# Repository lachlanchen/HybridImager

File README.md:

[English](README.md) · [العربية](i18n/README.ar.md) · [Español](i18n/README.es.md) · [Français](i18n/README.fr.md) · [日本語](i18n/README.ja.md) · [한국어](i18n/README.ko.md) · [Tiếng Việt](i18n/README.vi.md) · [中文 (简体)](i18n/README.zh-Hans.md) · [中文（繁體）](i18n/README.zh-Hant.md) · [Deutsch](i18n/README.de.md) · [Русский](i18n/README.ru.md)

# HybridImager

*Open hybrid scientific imaging: single-pixel, event, frame, and spectral sensing in one maintainable research stack.*

HybridImager is a research and design workspace for a mixed scientific detector. The concept combines a high-dynamic-range single-pixel bucket detector, event-camera timing, frame-camera texture, and optional spectral measurements under one synchronized data model.

<!-- support:start -->

<!-- support:end -->

## System Concept

- **Single-pixel branch:** a central low-noise detector/TIA path for absolute intensity, high dynamic range, and spectral or coded measurements.
- **Event branch:** asynchronous temporal contrast from commercial event cameras first, then open FPGA interfaces when practical.
- **Frame branch:** global-shutter frame modules for texture, calibration, and human-readable inspection.
- **Fusion layer:** timestamped streams with exposure, gain, calibration profile, trigger, and pattern metadata.

## V1 Sensor Board

The first board draft is a KiCad-generated **Weiqi sparse sensor carrier** with 21 single-pixel detector sites, not one central bucket only. It includes per-site signal pads, explicit ground routing, three AFE placeholders, a QFN timing placeholder, SMA sync in/out, power/sync header, and a 2x20 expansion header for later event/frame/tile work.

Review package: [`hardware/v1-weiqi-sensor/`](hardware/v1-weiqi-sensor/) contains the KiCad board, dataset, BOM, clean DRC JSON, STEP model, Gerbers, drill files, and full-view renders.

## V2 ALS-PT19 Matrix

V2 is a dense `32x32` sensor-board draft using the `ALS-PT19` phototransistor family from the `CustomSensor`/digiOBSCURA reference. Unlike the older 45-degree, 2.0 mm layout, V2 uses unrotated footprints on a `2.54 mm` pitch so each sensor pad, row header pin, and column header pin is aligned and routable.

Review package: [`hardware/v2-als-pt19-32x32/`](hardware/v2-als-pt19-32x32/) contains the KiCad board, CustomSensor source dataset, BOM, clean DRC JSON, STEP model, Gerbers, drill files, and full-view renders.

## Current Contents

| Area | Location |
| --- | --- |
| Concept paper | `publications/hybrid_camera_concept.pdf` |
| Open camera survey | `publications/open_camera_project_survey.pdf` |
| V1 sparse sensor board | `hardware/v1-weiqi-sensor/` |
| V2 aligned ALS-PT19 matrix | `hardware/v2-als-pt19-32x32/` |
| Research notes | `references/` |
| Deterministic diagrams | `figures/hybrid_board_layout.*`, `figures/hybrid_signal_chain.*` |
| Hardware plan | `hardware/board_architecture.md` |
| Reconstruction plan | `algorithms/reconstruction_plan.md` |
| Prior context | `copied-context/` |
| Open project mirrors | `external/` as git submodules |

## Quick Start

```bash
git clone --recurse-submodules https://github.com/lachlanchen/HybridImager.git
cd HybridImager
make all
```

If the repository is already cloned:

```bash
git submodule update --init --recursive
make survey
```

## Research Baseline

The strongest open single-pixel path is **ONE-PIX** plus **ONE-PIX_hardware**. For event vision, the realistic first build uses commercial event cameras with **OpenEB**, **jAER**, **v2e**, and **E2VID**. For frame hardware, the useful open references are **OneInchEye**, **Antmicro OV9281**, **AXIOM Beta**, and **Seeed reCamera**.

The project does not assume a custom event-sensor ASIC in the first stage. It starts with open board-level synchronization, open data formats, open reconstruction, and reusable mechanical/PCB references.

## CAD And Hardware Notes

Preferred Shapr3D export package for editable mechanical work:

```text
STEP + native .shapr + Parasolid + DXF from sketch + 3MF/STL preview
```

Use STEP as the main interchange format, Parasolid as the high-fidelity solid backup, DXF for 2D outlines and plates, and STL/3MF only for print or mesh preview.

## Build Commands

```bash
make figures   # regenerate deterministic diagrams
make paper     # compile the HybridImager concept paper
make survey    # compile the open camera project survey
make all       # run paper and survey builds
make clean     # remove LaTeX build byproducts
```

## Citation

If you use HybridImager in research, cite the repository. GitHub reads [CITATION.cff](CITATION.cff) and shows a **Cite this repository** panel on the repo page.

```bibtex
@software{chen_hybridimager_2026,
  author = {Chen, Lachlan},
  title = {HybridImager: Open Hybrid Scientific Imaging Research Workspace},
  year = {2026},
  url = {https://github.com/lachlanchen/HybridImager}
}
```

## Status

This is an early research workspace, not a certified imaging product. The immediate goal is a maintainable experiment pipeline for optical and microscopy setups: build with available modules, synchronize cleanly, reconstruct reproducibly, and only integrate custom hardware after the data contract is stable.

Build less. Image more.

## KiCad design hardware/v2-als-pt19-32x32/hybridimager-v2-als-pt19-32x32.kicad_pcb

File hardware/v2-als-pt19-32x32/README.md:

# HybridImager V2 ALS-PT19 32x32 Aligned Sensor Board

V2 moves from the sparse V1 detector carrier to a dense `32x32` matrix using
the same `ALS-PT19` phototransistor family documented in `CustomSensor`.

## What Changed From V1

- `1024` ALS-PT19 detector sites instead of 21 sparse sites.
- Unrotated footprints on a `2.54 mm` pitch so pins are aligned and pads do not overlap.
- Row pins align to the left edge header; column pins align to the top edge header.
- Row nets route horizontally on `F.Cu`; column nets route vertically on `B.Cu`.
- ADG732 row/column mux footprints remain as placement placeholders for the CustomSensor addressing model.

## Files

- `hybridimager-v2-als-pt19-32x32.kicad_pcb`: generated KiCad board.
- `hybridimager-v2-als-pt19-32x32.kicad_pro`: KiCad project file.
- `hybridimager-v2-als-pt19-32x32.kicad_sch`: board-first schematic stub.
- `hybridimager-v2-source-dataset.json`: source assumptions and CustomSensor reference dataset.
- `hybridimager-v2-bom.csv`: draft BOM.
- `artifacts/hybridimager-v2-full-view-render.png`: generated full-view 3D concept render.
- `artifacts/hybridimager-v2-kicad-render-full.png`: KiCad-native zoomed-out render.
- `artifacts/hybridimager-v2-kicad-render-close.png`: KiCad-native closer render.
- `artifacts/hybridimager-v2-als-pt19-32x32.step`: lightweight board-level STEP export.
- `gerber/`: Gerber and drill outputs.

## Reproduce

```bash
python3 scripts/generate_v2_als_pt19_32x32_board.py
kicad-cli pcb upgrade hardware/v2-als-pt19-32x32/hybridimager-v2-als-pt19-32x32.kicad_pcb
kicad-cli pcb drc --format json --severity-all -o hardware/v2-als-pt19-32x32/artifacts/drc.json hardware/v2-als-pt19-32x32/hybridimager-v2-als-pt19-32x32.kicad_pcb
kicad-cli pcb export step --force -o hardware/v2-als-pt19-32x32/artifacts/hybridimager-v2-als-pt19-32x32.step hardware/v2-als-pt19-32x32/hybridimager-v2-als-pt19-32x32.kicad_pcb
kicad-cli pcb export gerbers --layers F.Cu,B.Cu,F.SilkS,B.SilkS,F.Mask,B.Mask,Edge.Cuts,F.Fab,B.Fab --precision 6 --check-zones -o hardware/v2-als-pt19-32x32/gerber hardware/v2-als-pt19-32x32/hybridimager-v2-als-pt19-32x32.kicad_pcb
kicad-cli pcb export drill --generate-map --map-format svg --generate-report --report-path hardware/v2-als-pt19-32x32/artifacts/drill-report.txt -o hardware/v2-als-pt19-32x32/gerber hardware/v2-als-pt19-32x32/hybridimager-v2-als-pt19-32x32.kicad_pcb
xvfb-run -a kicad-cli pcb render --output hardware/v2-als-pt19-32x32/artifacts/hybridimager-v2-kicad-render-full.png --width 1800 --height 1200 --background opaque --quality high --floor --perspective --rotate 315,0,35 --zoom 0.95 hardware/v2-als-pt19-32x32/hybridimager-v2-als-pt19-32x32.kicad_pcb
```

## Engineering Status

Current generated validation: KiCad DRC reports 0 violations and 0 unconnected
items. Full-detail STEP with pad/track solidification is intentionally avoided
for this dense 1024-sensor matrix because it is much slower; use Gerbers for
electrical manufacturing geometry and the lightweight STEP for mechanical board
outline review.

This is a dense matrix layout draft, not a fabrication-approved design. It
still needs final ADG732 schematic wiring, optical masking/baffling decisions,
row/column crosstalk review, solderability review, and firmware pin mapping.

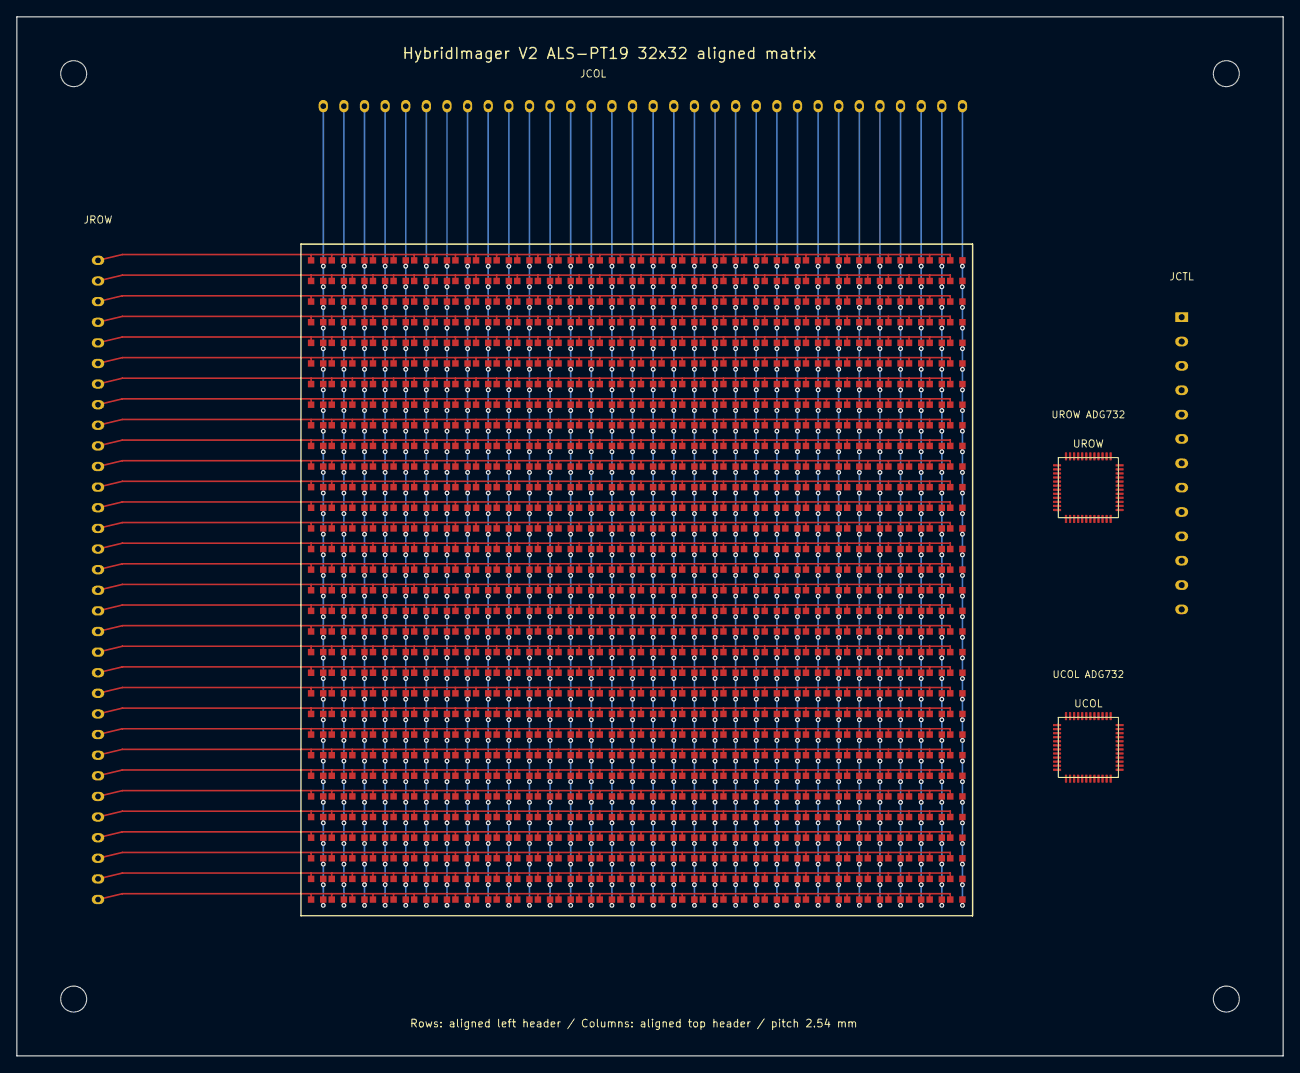
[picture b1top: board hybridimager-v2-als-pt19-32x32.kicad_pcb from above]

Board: 2 copper layers, 156.0 x 128.0 mm, 1033 parts (0 on the bottom side), 64 nets.

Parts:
H1, H2, H3, H4: M3; MountingHole_3.2mm_M3
JCOL: COL_EDGE_1x32_ALIGNED; Aligned_Col_Header_1x32_2.54mm
JCTL: ADDR_SYNC_PWR; Control_Header_1x13_3mm
JROW: ROW_EDGE_1x32_ALIGNED; Aligned_Row_Header_1x32_2.54mm
Q0101, Q0102, Q0103, Q0104, Q0105, Q0106, Q0107, Q0108, Q0109, Q0110, Q0111, Q0112, Q0113, Q0114, Q0115, Q0116, Q0117, Q0118, Q0119, Q0120, Q0121, Q0122, Q0123, Q0124, Q0125, Q0126, Q0127, Q0128, Q0129, Q0130, Q0131, Q0132, Q0201, Q0202, Q0203, Q0204, Q0205, Q0206, Q0207, Q0208, Q0209, Q0210, Q0211, Q0212, Q0213, Q0214, Q0215, Q0216, Q0217, Q0218, Q0219, Q0220, Q0221, Q0222, Q0223, Q0224, Q0225, Q0226, Q0227, Q0228, Q0229, Q0230, Q0231, Q0232, Q0301, Q0302, Q0303, Q0304, Q0305, Q0306, Q0307, Q0308, Q0309, Q0310, Q0311, Q0312, Q0313, Q0314, Q0315, Q0316, Q0317, Q0318, Q0319, Q0320, Q0321, Q0322, Q0323, Q0324, Q0325, Q0326, Q0327, Q0328, Q0329, Q0330, Q0331, Q0332, Q0401, Q0402, Q0403, Q0404, Q0405, Q0406, Q0407, Q0408, Q0409, Q0410, Q0411, Q0412, Q0413, Q0414, Q0415, Q0416, Q0417, Q0418, Q0419, Q0420, Q0421, Q0422, Q0423, Q0424, Q0425, Q0426, Q0427, Q0428, Q0429, Q0430, Q0431, Q0432, Q0501, Q0502, Q0503, Q0504, Q0505, Q0506, Q0507, Q0508, Q0509, Q0510, Q0511, Q0512, Q0513, Q0514, Q0515, Q0516, Q0517, Q0518, Q0519, Q0520, Q0521, Q0522, Q0523, Q0524, Q0525, Q0526, Q0527, Q0528, Q0529, Q0530, Q0531, Q0532, Q0601, Q0602, Q0603, Q0604, Q0605, Q0606, Q0607, Q0608, Q0609, Q0610, Q0611, Q0612, Q0613, Q0614, Q0615, Q0616, Q0617, Q0618, Q0619, Q0620, Q0621, Q0622, Q0623, Q0624, Q0625, Q0626, Q0627, Q0628, Q0629, Q0630, Q0631, Q0632, Q0701, Q0702, Q0703, Q0704, Q0705, Q0706, Q0707, Q0708, Q0709, Q0710, Q0711, Q0712, Q0713, Q0714, Q0715, Q0716, Q0717, Q0718, Q0719, Q0720, Q0721, Q0722, Q0723, Q0724, Q0725, Q0726, Q0727, Q0728, Q0729, Q0730, Q0731, Q0732, Q0801, Q0802, Q0803, Q0804, Q0805, Q0806, Q0807, Q0808, Q0809, Q0810, Q0811, Q0812, Q0813, Q0814, Q0815, Q0816, Q0817, Q0818, Q0819, Q0820, Q0821, Q0822, Q0823, Q0824, Q0825, Q0826, Q0827, Q0828, Q0829, Q0830, Q0831, Q0832, Q0901, Q0902, Q0903, Q0904, Q0905, Q0906, Q0907, Q0908, Q0909, Q0910, Q0911, Q0912, Q0913, Q0914, Q0915, Q0916, Q0917, Q0918, Q0919, Q0920, Q0921, Q0922, Q0923, Q0924, Q0925, Q0926, Q0927, Q0928, Q0929, Q0930, Q0931, Q0932, Q1001, Q1002, Q1003, Q1004, Q1005, Q1006, Q1007, Q1008, Q1009, Q1010, Q1011, Q1012, Q1013, Q1014, Q1015, Q1016, Q1017, Q1018, Q1019, Q1020, Q1021, Q1022, Q1023, Q1024, Q1025, Q1026, Q1027, Q1028, Q1029, Q1030, Q1031, Q1032, Q1101, Q1102, Q1103, Q1104, Q1105, Q1106, Q1107, Q1108, Q1109, Q1110, Q1111, Q1112, Q1113, Q1114, Q1115, Q1116, Q1117, Q1118, Q1119, Q1120, Q1121, Q1122, Q1123, Q1124, Q1125, Q1126, Q1127, Q1128, Q1129, Q1130, Q1131, Q1132, Q1201, Q1202, Q1203, Q1204, Q1205, Q1206, Q1207, Q1208, Q1209, Q1210, Q1211, Q1212, Q1213, Q1214, Q1215, Q1216, Q1217, Q1218, Q1219, Q1220, Q1221, Q1222, Q1223, Q1224, Q1225, Q1226, Q1227, Q1228, Q1229, Q1230, Q1231, Q1232, Q1301, Q1302, Q1303, Q1304, Q1305, Q1306, Q1307, Q1308, Q1309, Q1310, Q1311, Q1312, Q1313, Q1314, Q1315, Q1316, Q1317, Q1318, Q1319, Q1320, Q1321, Q1322, Q1323, Q1324, Q1325, Q1326, Q1327, Q1328, Q1329, Q1330, Q1331, Q1332, Q1401, Q1402, Q1403, Q1404, Q1405, Q1406, Q1407, Q1408, Q1409, Q1410, Q1411, Q1412, Q1413, Q1414, Q1415, Q1416, Q1417, Q1418, Q1419, Q1420, Q1421, Q1422, Q1423, Q1424, Q1425, Q1426, Q1427, Q1428, Q1429, Q1430, Q1431, Q1432, Q1501, Q1502, Q1503, Q1504, Q1505, Q1506, Q1507, Q1508, Q1509, Q1510, Q1511, Q1512, Q1513, Q1514, Q1515, Q1516, Q1517, Q1518, Q1519, Q1520, Q1521, Q1522, Q1523, Q1524, Q1525, Q1526, Q1527, Q1528, Q1529, Q1530, Q1531, Q1532, Q1601, Q1602, Q1603, Q1604, Q1605, Q1606, Q1607, Q1608, Q1609, Q1610, Q1611, Q1612, Q1613, Q1614, Q1615, Q1616, Q1617, Q1618, Q1619, Q1620, Q1621, Q1622, Q1623, Q1624, Q1625, Q1626, Q1627, Q1628, Q1629, Q1630, Q1631, Q1632, Q1701, Q1702, Q1703, Q1704, Q1705, Q1706, Q1707, Q1708, Q1709, Q1710, Q1711, Q1712, Q1713, Q1714, Q1715, Q1716, Q1717, Q1718, Q1719, Q1720, Q1721, Q1722, Q1723, Q1724, Q1725, Q1726, Q1727, Q1728, Q1729, Q1730, Q1731, Q1732, Q1801, Q1802, Q1803, Q1804, Q1805, Q1806, Q1807, Q1808, Q1809, Q1810, Q1811, Q1812, Q1813, Q1814, Q1815, Q1816, Q1817, Q1818, Q1819, Q1820, Q1821, Q1822, Q1823, Q1824, Q1825, Q1826, Q1827, Q1828, Q1829, Q1830, Q1831, Q1832, Q1901, Q1902, Q1903, Q1904, Q1905, Q1906, Q1907, Q1908, Q1909, Q1910, Q1911, Q1912, Q1913, Q1914, Q1915, Q1916, Q1917, Q1918, Q1919, Q1920, Q1921, Q1922, Q1923, Q1924, Q1925, Q1926, Q1927, Q1928, Q1929, Q1930, Q1931, Q1932, Q2001, Q2002, Q2003, Q2004, Q2005, Q2006, Q2007, Q2008, Q2009, Q2010, Q2011, Q2012, Q2013, Q2014, Q2015, Q2016, Q2017, Q2018, Q2019, Q2020, Q2021, Q2022, Q2023, Q2024, Q2025, Q2026, Q2027, Q2028, Q2029, Q2030, Q2031, Q2032, Q2101, Q2102, Q2103, Q2104, Q2105, Q2106, Q2107, Q2108, Q2109, Q2110, Q2111, Q2112, Q2113, Q2114, Q2115, Q2116, Q2117, Q2118, Q2119, Q2120, Q2121, Q2122, Q2123, Q2124, Q2125, Q2126, Q2127, Q2128, Q2129, Q2130, Q2131, Q2132, Q2201, Q2202, Q2203, Q2204, Q2205, Q2206, Q2207, Q2208, Q2209, Q2210, Q2211, Q2212, Q2213, Q2214, Q2215, Q2216, Q2217, Q2218, Q2219, Q2220, Q2221, Q2222, Q2223, Q2224, Q2225, Q2226, Q2227, Q2228, Q2229, Q2230, Q2231, Q2232, Q2301, Q2302, Q2303, Q2304, Q2305, Q2306, Q2307, Q2308, Q2309, Q2310, Q2311, Q2312, Q2313, Q2314, Q2315, Q2316, Q2317, Q2318, Q2319, Q2320, Q2321, Q2322, Q2323, Q2324, Q2325, Q2326, Q2327, Q2328, Q2329, Q2330, Q2331, Q2332, Q2401, Q2402, Q2403, Q2404, Q2405, Q2406, Q2407, Q2408, Q2409, Q2410, Q2411, Q2412, Q2413, Q2414, Q2415, Q2416, Q2417, Q2418, Q2419, Q2420, Q2421, Q2422, Q2423, Q2424, Q2425, Q2426, Q2427, Q2428, Q2429, Q2430, Q2431, Q2432, Q2501, Q2502, Q2503, Q2504, Q2505, Q2506, Q2507, Q2508, Q2509, Q2510, Q2511, Q2512, Q2513, Q2514, Q2515, Q2516, Q2517, Q2518, Q2519, Q2520, Q2521, Q2522, Q2523, Q2524, Q2525, Q2526, Q2527, Q2528, Q2529, Q2530, Q2531, Q2532, Q2601, Q2602, Q2603, Q2604, Q2605, Q2606, Q2607, Q2608, Q2609, Q2610, Q2611, Q2612, Q2613, Q2614, Q2615, Q2616, Q2617, Q2618, Q2619, Q2620, Q2621, Q2622, Q2623, Q2624, Q2625, Q2626, Q2627, Q2628, Q2629, Q2630, Q2631, Q2632, Q2701, Q2702, Q2703, Q2704, Q2705, Q2706, Q2707, Q2708, Q2709, Q2710, Q2711, Q2712, Q2713, Q2714, Q2715, Q2716, Q2717, Q2718, Q2719, Q2720, Q2721, Q2722, Q2723, Q2724, Q2725, Q2726, Q2727, Q2728, Q2729, Q2730, Q2731, Q2732, Q2801, Q2802, Q2803, Q2804, Q2805, Q2806, Q2807, Q2808, Q2809, Q2810, Q2811, Q2812, Q2813, Q2814, Q2815, Q2816, Q2817, Q2818, Q2819, Q2820, Q2821, Q2822, Q2823, Q2824, Q2825, Q2826, Q2827, Q2828, Q2829, Q2830, Q2831, Q2832, Q2901, Q2902, Q2903, Q2904, Q2905, Q2906, Q2907, Q2908, Q2909, Q2910, Q2911, Q2912, Q2913, Q2914, Q2915, Q2916, Q2917, Q2918, Q2919, Q2920, Q2921, Q2922, Q2923, Q2924, Q2925, Q2926, Q2927, Q2928, Q2929, Q2930, Q2931, Q2932, Q3001, Q3002, Q3003, Q3004, Q3005, Q3006, Q3007, Q3008, Q3009, Q3010, Q3011, Q3012, Q3013, Q3014, Q3015, Q3016, Q3017, Q3018, Q3019, Q3020, Q3021, Q3022, Q3023, Q3024, Q3025, Q3026, Q3027, Q3028, Q3029, Q3030, Q3031, Q3032, Q3101, Q3102, Q3103, Q3104, Q3105, Q3106, Q3107, Q3108, Q3109, Q3110, Q3111, Q3112, Q3113, Q3114, Q3115, Q3116, Q3117, Q3118, Q3119, Q3120, Q3121, Q3122, Q3123, Q3124, Q3125, Q3126, Q3127, Q3128, Q3129, Q3130, Q3131, Q3132, Q3201, Q3202, Q3203, Q3204, Q3205, Q3206, Q3207, Q3208, Q3209, Q3210, Q3211, Q3212, Q3213, Q3214, Q3215, Q3216, Q3217, Q3218, Q3219, Q3220, Q3221, Q3222, Q3223, Q3224, Q3225, Q3226, Q3227, Q3228, Q3229, Q3230, Q3231, Q3232: ALS-PT19
UCOL: ADG732_32_TO_1_PLACEHOLDER; ADG732_TQFP48_PLACEHOLDER
UROW: ADG732_32_TO_1_PLACEHOLDER; ADG732_TQFP48_PLACEHOLDER

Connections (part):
COL01: JCOL.1 (COL01), Q0101.2 (COL), Q0201.2 (COL), Q0301.2 (COL), Q0401.2 (COL), Q0501.2 (COL), Q0601.2 (COL), Q0701.2 (COL), Q0801.2 (COL), Q0901.2 (COL), Q1001.2 (COL), Q1101.2 (COL), Q1201.2 (COL), Q1301.2 (COL), Q1401.2 (COL), Q1501.2 (COL), Q1601.2 (COL), Q1701.2 (COL), Q1801.2 (COL), Q1901.2 (COL), Q2001.2 (COL), Q2101.2 (COL), Q2201.2 (COL), Q2301.2 (COL), Q2401.2 (COL), Q2501.2 (COL), Q2601.2 (COL), Q2701.2 (COL), Q2801.2 (COL), Q2901.2 (COL), Q3001.2 (COL), Q3101.2 (COL), Q3201.2 (COL)
COL02: JCOL.2 (COL02), Q0102.2 (COL), Q0202.2 (COL), Q0302.2 (COL), Q0402.2 (COL), Q0502.2 (COL), Q0602.2 (COL), Q0702.2 (COL), Q0802.2 (COL), Q0902.2 (COL), Q1002.2 (COL), Q1102.2 (COL), Q1202.2 (COL), Q1302.2 (COL), Q1402.2 (COL), Q1502.2 (COL), Q1602.2 (COL), Q1702.2 (COL), Q1802.2 (COL), Q1902.2 (COL), Q2002.2 (COL), Q2102.2 (COL), Q2202.2 (COL), Q2302.2 (COL), Q2402.2 (COL), Q2502.2 (COL), Q2602.2 (COL), Q2702.2 (COL), Q2802.2 (COL), Q2902.2 (COL), Q3002.2 (COL), Q3102.2 (COL), Q3202.2 (COL)
COL03: JCOL.3 (COL03), Q0103.2 (COL), Q0203.2 (COL), Q0303.2 (COL), Q0403.2 (COL), Q0503.2 (COL), Q0603.2 (COL), Q0703.2 (COL), Q0803.2 (COL), Q0903.2 (COL), Q1003.2 (COL), Q1103.2 (COL), Q1203.2 (COL), Q1303.2 (COL), Q1403.2 (COL), Q1503.2 (COL), Q1603.2 (COL), Q1703.2 (COL), Q1803.2 (COL), Q1903.2 (COL), Q2003.2 (COL), Q2103.2 (COL), Q2203.2 (COL), Q2303.2 (COL), Q2403.2 (COL), Q2503.2 (COL), Q2603.2 (COL), Q2703.2 (COL), Q2803.2 (COL), Q2903.2 (COL), Q3003.2 (COL), Q3103.2 (COL), Q3203.2 (COL)
COL04: JCOL.4 (COL04), Q0104.2 (COL), Q0204.2 (COL), Q0304.2 (COL), Q0404.2 (COL), Q0504.2 (COL), Q0604.2 (COL), Q0704.2 (COL), Q0804.2 (COL), Q0904.2 (COL), Q1004.2 (COL), Q1104.2 (COL), Q1204.2 (COL), Q1304.2 (COL), Q1404.2 (COL), Q1504.2 (COL), Q1604.2 (COL), Q1704.2 (COL), Q1804.2 (COL), Q1904.2 (COL), Q2004.2 (COL), Q2104.2 (COL), Q2204.2 (COL), Q2304.2 (COL), Q2404.2 (COL), Q2504.2 (COL), Q2604.2 (COL), Q2704.2 (COL), Q2804.2 (COL), Q2904.2 (COL), Q3004.2 (COL), Q3104.2 (COL), Q3204.2 (COL)
COL05: JCOL.5 (COL05), Q0105.2 (COL), Q0205.2 (COL), Q0305.2 (COL), Q0405.2 (COL), Q0505.2 (COL), Q0605.2 (COL), Q0705.2 (COL), Q0805.2 (COL), Q0905.2 (COL), Q1005.2 (COL), Q1105.2 (COL), Q1205.2 (COL), Q1305.2 (COL), Q1405.2 (COL), Q1505.2 (COL), Q1605.2 (COL), Q1705.2 (COL), Q1805.2 (COL), Q1905.2 (COL), Q2005.2 (COL), Q2105.2 (COL), Q2205.2 (COL), Q2305.2 (COL), Q2405.2 (COL), Q2505.2 (COL), Q2605.2 (COL), Q2705.2 (COL), Q2805.2 (COL), Q2905.2 (COL), Q3005.2 (COL), Q3105.2 (COL), Q3205.2 (COL)
COL06: JCOL.6 (COL06), Q0106.2 (COL), Q0206.2 (COL), Q0306.2 (COL), Q0406.2 (COL), Q0506.2 (COL), Q0606.2 (COL), Q0706.2 (COL), Q0806.2 (COL), Q0906.2 (COL), Q1006.2 (COL), Q1106.2 (COL), Q1206.2 (COL), Q1306.2 (COL), Q1406.2 (COL), Q1506.2 (COL), Q1606.2 (COL), Q1706.2 (COL), Q1806.2 (COL), Q1906.2 (COL), Q2006.2 (COL), Q2106.2 (COL), Q2206.2 (COL), Q2306.2 (COL), Q2406.2 (COL), Q2506.2 (COL), Q2606.2 (COL), Q2706.2 (COL), Q2806.2 (COL), Q2906.2 (COL), Q3006.2 (COL), Q3106.2 (COL), Q3206.2 (COL)
COL07: JCOL.7 (COL07), Q0107.2 (COL), Q0207.2 (COL), Q0307.2 (COL), Q0407.2 (COL), Q0507.2 (COL), Q0607.2 (COL), Q0707.2 (COL), Q0807.2 (COL), Q0907.2 (COL), Q1007.2 (COL), Q1107.2 (COL), Q1207.2 (COL), Q1307.2 (COL), Q1407.2 (COL), Q1507.2 (COL), Q1607.2 (COL), Q1707.2 (COL), Q1807.2 (COL), Q1907.2 (COL), Q2007.2 (COL), Q2107.2 (COL), Q2207.2 (COL), Q2307.2 (COL), Q2407.2 (COL), Q2507.2 (COL), Q2607.2 (COL), Q2707.2 (COL), Q2807.2 (COL), Q2907.2 (COL), Q3007.2 (COL), Q3107.2 (COL), Q3207.2 (COL)
COL08: JCOL.8 (COL08), Q0108.2 (COL), Q0208.2 (COL), Q0308.2 (COL), Q0408.2 (COL), Q0508.2 (COL), Q0608.2 (COL), Q0708.2 (COL), Q0808.2 (COL), Q0908.2 (COL), Q1008.2 (COL), Q1108.2 (COL), Q1208.2 (COL), Q1308.2 (COL), Q1408.2 (COL), Q1508.2 (COL), Q1608.2 (COL), Q1708.2 (COL), Q1808.2 (COL), Q1908.2 (COL), Q2008.2 (COL), Q2108.2 (COL), Q2208.2 (COL), Q2308.2 (COL), Q2408.2 (COL), Q2508.2 (COL), Q2608.2 (COL), Q2708.2 (COL), Q2808.2 (COL), Q2908.2 (COL), Q3008.2 (COL), Q3108.2 (COL), Q3208.2 (COL)
COL09: JCOL.9 (COL09), Q0109.2 (COL), Q0209.2 (COL), Q0309.2 (COL), Q0409.2 (COL), Q0509.2 (COL), Q0609.2 (COL), Q0709.2 (COL), Q0809.2 (COL), Q0909.2 (COL), Q1009.2 (COL), Q1109.2 (COL), Q1209.2 (COL), Q1309.2 (COL), Q1409.2 (COL), Q1509.2 (COL), Q1609.2 (COL), Q1709.2 (COL), Q1809.2 (COL), Q1909.2 (COL), Q2009.2 (COL), Q2109.2 (COL), Q2209.2 (COL), Q2309.2 (COL), Q2409.2 (COL), Q2509.2 (COL), Q2609.2 (COL), Q2709.2 (COL), Q2809.2 (COL), Q2909.2 (COL), Q3009.2 (COL), Q3109.2 (COL), Q3209.2 (COL)
COL10: JCOL.10 (COL10), Q0110.2 (COL), Q0210.2 (COL), Q0310.2 (COL), Q0410.2 (COL), Q0510.2 (COL), Q0610.2 (COL), Q0710.2 (COL), Q0810.2 (COL), Q0910.2 (COL), Q1010.2 (COL), Q1110.2 (COL), Q1210.2 (COL), Q1310.2 (COL), Q1410.2 (COL), Q1510.2 (COL), Q1610.2 (COL), Q1710.2 (COL), Q1810.2 (COL), Q1910.2 (COL), Q2010.2 (COL), Q2110.2 (COL), Q2210.2 (COL), Q2310.2 (COL), Q2410.2 (COL), Q2510.2 (COL), Q2610.2 (COL), Q2710.2 (COL), Q2810.2 (COL), Q2910.2 (COL), Q3010.2 (COL), Q3110.2 (COL), Q3210.2 (COL)
COL11: JCOL.11 (COL11), Q0111.2 (COL), Q0211.2 (COL), Q0311.2 (COL), Q0411.2 (COL), Q0511.2 (COL), Q0611.2 (COL), Q0711.2 (COL), Q0811.2 (COL), Q0911.2 (COL), Q1011.2 (COL), Q1111.2 (COL), Q1211.2 (COL), Q1311.2 (COL), Q1411.2 (COL), Q1511.2 (COL), Q1611.2 (COL), Q1711.2 (COL), Q1811.2 (COL), Q1911.2 (COL), Q2011.2 (COL), Q2111.2 (COL), Q2211.2 (COL), Q2311.2 (COL), Q2411.2 (COL), Q2511.2 (COL), Q2611.2 (COL), Q2711.2 (COL), Q2811.2 (COL), Q2911.2 (COL), Q3011.2 (COL), Q3111.2 (COL), Q3211.2 (COL)
COL12: JCOL.12 (COL12), Q0112.2 (COL), Q0212.2 (COL), Q0312.2 (COL), Q0412.2 (COL), Q0512.2 (COL), Q0612.2 (COL), Q0712.2 (COL), Q0812.2 (COL), Q0912.2 (COL), Q1012.2 (COL), Q1112.2 (COL), Q1212.2 (COL), Q1312.2 (COL), Q1412.2 (COL), Q1512.2 (COL), Q1612.2 (COL), Q1712.2 (COL), Q1812.2 (COL), Q1912.2 (COL), Q2012.2 (COL), Q2112.2 (COL), Q2212.2 (COL), Q2312.2 (COL), Q2412.2 (COL), Q2512.2 (COL), Q2612.2 (COL), Q2712.2 (COL), Q2812.2 (COL), Q2912.2 (COL), Q3012.2 (COL), Q3112.2 (COL), Q3212.2 (COL)
COL13: JCOL.13 (COL13), Q0113.2 (COL), Q0213.2 (COL), Q0313.2 (COL), Q0413.2 (COL), Q0513.2 (COL), Q0613.2 (COL), Q0713.2 (COL), Q0813.2 (COL), Q0913.2 (COL), Q1013.2 (COL), Q1113.2 (COL), Q1213.2 (COL), Q1313.2 (COL), Q1413.2 (COL), Q1513.2 (COL), Q1613.2 (COL), Q1713.2 (COL), Q1813.2 (COL), Q1913.2 (COL), Q2013.2 (COL), Q2113.2 (COL), Q2213.2 (COL), Q2313.2 (COL), Q2413.2 (COL), Q2513.2 (COL), Q2613.2 (COL), Q2713.2 (COL), Q2813.2 (COL), Q2913.2 (COL), Q3013.2 (COL), Q3113.2 (COL), Q3213.2 (COL)
COL14: JCOL.14 (COL14), Q0114.2 (COL), Q0214.2 (COL), Q0314.2 (COL), Q0414.2 (COL), Q0514.2 (COL), Q0614.2 (COL), Q0714.2 (COL), Q0814.2 (COL), Q0914.2 (COL), Q1014.2 (COL), Q1114.2 (COL), Q1214.2 (COL), Q1314.2 (COL), Q1414.2 (COL), Q1514.2 (COL), Q1614.2 (COL), Q1714.2 (COL), Q1814.2 (COL), Q1914.2 (COL), Q2014.2 (COL), Q2114.2 (COL), Q2214.2 (COL), Q2314.2 (COL), Q2414.2 (COL), Q2514.2 (COL), Q2614.2 (COL), Q2714.2 (COL), Q2814.2 (COL), Q2914.2 (COL), Q3014.2 (COL), Q3114.2 (COL), Q3214.2 (COL)
COL15: JCOL.15 (COL15), Q0115.2 (COL), Q0215.2 (COL), Q0315.2 (COL), Q0415.2 (COL), Q0515.2 (COL), Q0615.2 (COL), Q0715.2 (COL), Q0815.2 (COL), Q0915.2 (COL), Q1015.2 (COL), Q1115.2 (COL), Q1215.2 (COL), Q1315.2 (COL), Q1415.2 (COL), Q1515.2 (COL), Q1615.2 (COL), Q1715.2 (COL), Q1815.2 (COL), Q1915.2 (COL), Q2015.2 (COL), Q2115.2 (COL), Q2215.2 (COL), Q2315.2 (COL), Q2415.2 (COL), Q2515.2 (COL), Q2615.2 (COL), Q2715.2 (COL), Q2815.2 (COL), Q2915.2 (COL), Q3015.2 (COL), Q3115.2 (COL), Q3215.2 (COL)
COL16: JCOL.16 (COL16), Q0116.2 (COL), Q0216.2 (COL), Q0316.2 (COL), Q0416.2 (COL), Q0516.2 (COL), Q0616.2 (COL), Q0716.2 (COL), Q0816.2 (COL), Q0916.2 (COL), Q1016.2 (COL), Q1116.2 (COL), Q1216.2 (COL), Q1316.2 (COL), Q1416.2 (COL), Q1516.2 (COL), Q1616.2 (COL), Q1716.2 (COL), Q1816.2 (COL), Q1916.2 (COL), Q2016.2 (COL), Q2116.2 (COL), Q2216.2 (COL), Q2316.2 (COL), Q2416.2 (COL), Q2516.2 (COL), Q2616.2 (COL), Q2716.2 (COL), Q2816.2 (COL), Q2916.2 (COL), Q3016.2 (COL), Q3116.2 (COL), Q3216.2 (COL)
COL17: JCOL.17 (COL17), Q0117.2 (COL), Q0217.2 (COL), Q0317.2 (COL), Q0417.2 (COL), Q0517.2 (COL), Q0617.2 (COL), Q0717.2 (COL), Q0817.2 (COL), Q0917.2 (COL), Q1017.2 (COL), Q1117.2 (COL), Q1217.2 (COL), Q1317.2 (COL), Q1417.2 (COL), Q1517.2 (COL), Q1617.2 (COL), Q1717.2 (COL), Q1817.2 (COL), Q1917.2 (COL), Q2017.2 (COL), Q2117.2 (COL), Q2217.2 (COL), Q2317.2 (COL), Q2417.2 (COL), Q2517.2 (COL), Q2617.2 (COL), Q2717.2 (COL), Q2817.2 (COL), Q2917.2 (COL), Q3017.2 (COL), Q3117.2 (COL), Q3217.2 (COL)
COL18: JCOL.18 (COL18), Q0118.2 (COL), Q0218.2 (COL), Q0318.2 (COL), Q0418.2 (COL), Q0518.2 (COL), Q0618.2 (COL), Q0718.2 (COL), Q0818.2 (COL), Q0918.2 (COL), Q1018.2 (COL), Q1118.2 (COL), Q1218.2 (COL), Q1318.2 (COL), Q1418.2 (COL), Q1518.2 (COL), Q1618.2 (COL), Q1718.2 (COL), Q1818.2 (COL), Q1918.2 (COL), Q2018.2 (COL), Q2118.2 (COL), Q2218.2 (COL), Q2318.2 (COL), Q2418.2 (COL), Q2518.2 (COL), Q2618.2 (COL), Q2718.2 (COL), Q2818.2 (COL), Q2918.2 (COL), Q3018.2 (COL), Q3118.2 (COL), Q3218.2 (COL)
COL19: JCOL.19 (COL19), Q0119.2 (COL), Q0219.2 (COL), Q0319.2 (COL), Q0419.2 (COL), Q0519.2 (COL), Q0619.2 (COL), Q0719.2 (COL), Q0819.2 (COL), Q0919.2 (COL), Q1019.2 (COL), Q1119.2 (COL), Q1219.2 (COL), Q1319.2 (COL), Q1419.2 (COL), Q1519.2 (COL), Q1619.2 (COL), Q1719.2 (COL), Q1819.2 (COL), Q1919.2 (COL), Q2019.2 (COL), Q2119.2 (COL), Q2219.2 (COL), Q2319.2 (COL), Q2419.2 (COL), Q2519.2 (COL), Q2619.2 (COL), Q2719.2 (COL), Q2819.2 (COL), Q2919.2 (COL), Q3019.2 (COL), Q3119.2 (COL), Q3219.2 (COL)
COL20: JCOL.20 (COL20), Q0120.2 (COL), Q0220.2 (COL), Q0320.2 (COL), Q0420.2 (COL), Q0520.2 (COL), Q0620.2 (COL), Q0720.2 (COL), Q0820.2 (COL), Q0920.2 (COL), Q1020.2 (COL), Q1120.2 (COL), Q1220.2 (COL), Q1320.2 (COL), Q1420.2 (COL), Q1520.2 (COL), Q1620.2 (COL), Q1720.2 (COL), Q1820.2 (COL), Q1920.2 (COL), Q2020.2 (COL), Q2120.2 (COL), Q2220.2 (COL), Q2320.2 (COL), Q2420.2 (COL), Q2520.2 (COL), Q2620.2 (COL), Q2720.2 (COL), Q2820.2 (COL), Q2920.2 (COL), Q3020.2 (COL), Q3120.2 (COL), Q3220.2 (COL)
COL21: JCOL.21 (COL21), Q0121.2 (COL), Q0221.2 (COL), Q0321.2 (COL), Q0421.2 (COL), Q0521.2 (COL), Q0621.2 (COL), Q0721.2 (COL), Q0821.2 (COL), Q0921.2 (COL), Q1021.2 (COL), Q1121.2 (COL), Q1221.2 (COL), Q1321.2 (COL), Q1421.2 (COL), Q1521.2 (COL), Q1621.2 (COL), Q1721.2 (COL), Q1821.2 (COL), Q1921.2 (COL), Q2021.2 (COL), Q2121.2 (COL), Q2221.2 (COL), Q2321.2 (COL), Q2421.2 (COL), Q2521.2 (COL), Q2621.2 (COL), Q2721.2 (COL), Q2821.2 (COL), Q2921.2 (COL), Q3021.2 (COL), Q3121.2 (COL), Q3221.2 (COL)
COL22: JCOL.22 (COL22), Q0122.2 (COL), Q0222.2 (COL), Q0322.2 (COL), Q0422.2 (COL), Q0522.2 (COL), Q0622.2 (COL), Q0722.2 (COL), Q0822.2 (COL), Q0922.2 (COL), Q1022.2 (COL), Q1122.2 (COL), Q1222.2 (COL), Q1322.2 (COL), Q1422.2 (COL), Q1522.2 (COL), Q1622.2 (COL), Q1722.2 (COL), Q1822.2 (COL), Q1922.2 (COL), Q2022.2 (COL), Q2122.2 (COL), Q2222.2 (COL), Q2322.2 (COL), Q2422.2 (COL), Q2522.2 (COL), Q2622.2 (COL), Q2722.2 (COL), Q2822.2 (COL), Q2922.2 (COL), Q3022.2 (COL), Q3122.2 (COL), Q3222.2 (COL)
COL23: JCOL.23 (COL23), Q0123.2 (COL), Q0223.2 (COL), Q0323.2 (COL), Q0423.2 (COL), Q0523.2 (COL), Q0623.2 (COL), Q0723.2 (COL), Q0823.2 (COL), Q0923.2 (COL), Q1023.2 (COL), Q1123.2 (COL), Q1223.2 (COL), Q1323.2 (COL), Q1423.2 (COL), Q1523.2 (COL), Q1623.2 (COL), Q1723.2 (COL), Q1823.2 (COL), Q1923.2 (COL), Q2023.2 (COL), Q2123.2 (COL), Q2223.2 (COL), Q2323.2 (COL), Q2423.2 (COL), Q2523.2 (COL), Q2623.2 (COL), Q2723.2 (COL), Q2823.2 (COL), Q2923.2 (COL), Q3023.2 (COL), Q3123.2 (COL), Q3223.2 (COL)
COL24: JCOL.24 (COL24), Q0124.2 (COL), Q0224.2 (COL), Q0324.2 (COL), Q0424.2 (COL), Q0524.2 (COL), Q0624.2 (COL), Q0724.2 (COL), Q0824.2 (COL), Q0924.2 (COL), Q1024.2 (COL), Q1124.2 (COL), Q1224.2 (COL), Q1324.2 (COL), Q1424.2 (COL), Q1524.2 (COL), Q1624.2 (COL), Q1724.2 (COL), Q1824.2 (COL), Q1924.2 (COL), Q2024.2 (COL), Q2124.2 (COL), Q2224.2 (COL), Q2324.2 (COL), Q2424.2 (COL), Q2524.2 (COL), Q2624.2 (COL), Q2724.2 (COL), Q2824.2 (COL), Q2924.2 (COL), Q3024.2 (COL), Q3124.2 (COL), Q3224.2 (COL)
COL25: JCOL.25 (COL25), Q0125.2 (COL), Q0225.2 (COL), Q0325.2 (COL), Q0425.2 (COL), Q0525.2 (COL), Q0625.2 (COL), Q0725.2 (COL), Q0825.2 (COL), Q0925.2 (COL), Q1025.2 (COL), Q1125.2 (COL), Q1225.2 (COL), Q1325.2 (COL), Q1425.2 (COL), Q1525.2 (COL), Q1625.2 (COL), Q1725.2 (COL), Q1825.2 (COL), Q1925.2 (COL), Q2025.2 (COL), Q2125.2 (COL), Q2225.2 (COL), Q2325.2 (COL), Q2425.2 (COL), Q2525.2 (COL), Q2625.2 (COL), Q2725.2 (COL), Q2825.2 (COL), Q2925.2 (COL), Q3025.2 (COL), Q3125.2 (COL), Q3225.2 (COL)
COL26: JCOL.26 (COL26), Q0126.2 (COL), Q0226.2 (COL), Q0326.2 (COL), Q0426.2 (COL), Q0526.2 (COL), Q0626.2 (COL), Q0726.2 (COL), Q0826.2 (COL), Q0926.2 (COL), Q1026.2 (COL), Q1126.2 (COL), Q1226.2 (COL), Q1326.2 (COL), Q1426.2 (COL), Q1526.2 (COL), Q1626.2 (COL), Q1726.2 (COL), Q1826.2 (COL), Q1926.2 (COL), Q2026.2 (COL), Q2126.2 (COL), Q2226.2 (COL), Q2326.2 (COL), Q2426.2 (COL), Q2526.2 (COL), Q2626.2 (COL), Q2726.2 (COL), Q2826.2 (COL), Q2926.2 (COL), Q3026.2 (COL), Q3126.2 (COL), Q3226.2 (COL)
COL27: JCOL.27 (COL27), Q0127.2 (COL), Q0227.2 (COL), Q0327.2 (COL), Q0427.2 (COL), Q0527.2 (COL), Q0627.2 (COL), Q0727.2 (COL), Q0827.2 (COL), Q0927.2 (COL), Q1027.2 (COL), Q1127.2 (COL), Q1227.2 (COL), Q1327.2 (COL), Q1427.2 (COL), Q1527.2 (COL), Q1627.2 (COL), Q1727.2 (COL), Q1827.2 (COL), Q1927.2 (COL), Q2027.2 (COL), Q2127.2 (COL), Q2227.2 (COL), Q2327.2 (COL), Q2427.2 (COL), Q2527.2 (COL), Q2627.2 (COL), Q2727.2 (COL), Q2827.2 (COL), Q2927.2 (COL), Q3027.2 (COL), Q3127.2 (COL), Q3227.2 (COL)
COL28: JCOL.28 (COL28), Q0128.2 (COL), Q0228.2 (COL), Q0328.2 (COL), Q0428.2 (COL), Q0528.2 (COL), Q0628.2 (COL), Q0728.2 (COL), Q0828.2 (COL), Q0928.2 (COL), Q1028.2 (COL), Q1128.2 (COL), Q1228.2 (COL), Q1328.2 (COL), Q1428.2 (COL), Q1528.2 (COL), Q1628.2 (COL), Q1728.2 (COL), Q1828.2 (COL), Q1928.2 (COL), Q2028.2 (COL), Q2128.2 (COL), Q2228.2 (COL), Q2328.2 (COL), Q2428.2 (COL), Q2528.2 (COL), Q2628.2 (COL), Q2728.2 (COL), Q2828.2 (COL), Q2928.2 (COL), Q3028.2 (COL), Q3128.2 (COL), Q3228.2 (COL)
COL29: JCOL.29 (COL29), Q0129.2 (COL), Q0229.2 (COL), Q0329.2 (COL), Q0429.2 (COL), Q0529.2 (COL), Q0629.2 (COL), Q0729.2 (COL), Q0829.2 (COL), Q0929.2 (COL), Q1029.2 (COL), Q1129.2 (COL), Q1229.2 (COL), Q1329.2 (COL), Q1429.2 (COL), Q1529.2 (COL), Q1629.2 (COL), Q1729.2 (COL), Q1829.2 (COL), Q1929.2 (COL), Q2029.2 (COL), Q2129.2 (COL), Q2229.2 (COL), Q2329.2 (COL), Q2429.2 (COL), Q2529.2 (COL), Q2629.2 (COL), Q2729.2 (COL), Q2829.2 (COL), Q2929.2 (COL), Q3029.2 (COL), Q3129.2 (COL), Q3229.2 (COL)
COL30: JCOL.30 (COL30), Q0130.2 (COL), Q0230.2 (COL), Q0330.2 (COL), Q0430.2 (COL), Q0530.2 (COL), Q0630.2 (COL), Q0730.2 (COL), Q0830.2 (COL), Q0930.2 (COL), Q1030.2 (COL), Q1130.2 (COL), Q1230.2 (COL), Q1330.2 (COL), Q1430.2 (COL), Q1530.2 (COL), Q1630.2 (COL), Q1730.2 (COL), Q1830.2 (COL), Q1930.2 (COL), Q2030.2 (COL), Q2130.2 (COL), Q2230.2 (COL), Q2330.2 (COL), Q2430.2 (COL), Q2530.2 (COL), Q2630.2 (COL), Q2730.2 (COL), Q2830.2 (COL), Q2930.2 (COL), Q3030.2 (COL), Q3130.2 (COL), Q3230.2 (COL)
COL31: JCOL.31 (COL31), Q0131.2 (COL), Q0231.2 (COL), Q0331.2 (COL), Q0431.2 (COL), Q0531.2 (COL), Q0631.2 (COL), Q0731.2 (COL), Q0831.2 (COL), Q0931.2 (COL), Q1031.2 (COL), Q1131.2 (COL), Q1231.2 (COL), Q1331.2 (COL), Q1431.2 (COL), Q1531.2 (COL), Q1631.2 (COL), Q1731.2 (COL), Q1831.2 (COL), Q1931.2 (COL), Q2031.2 (COL), Q2131.2 (COL), Q2231.2 (COL), Q2331.2 (COL), Q2431.2 (COL), Q2531.2 (COL), Q2631.2 (COL), Q2731.2 (COL), Q2831.2 (COL), Q2931.2 (COL), Q3031.2 (COL), Q3131.2 (COL), Q3231.2 (COL)
COL32: JCOL.32 (COL32), Q0132.2 (COL), Q0232.2 (COL), Q0332.2 (COL), Q0432.2 (COL), Q0532.2 (COL), Q0632.2 (COL), Q0732.2 (COL), Q0832.2 (COL), Q0932.2 (COL), Q1032.2 (COL), Q1132.2 (COL), Q1232.2 (COL), Q1332.2 (COL), Q1432.2 (COL), Q1532.2 (COL), Q1632.2 (COL), Q1732.2 (COL), Q1832.2 (COL), Q1932.2 (COL), Q2032.2 (COL), Q2132.2 (COL), Q2232.2 (COL), Q2332.2 (COL), Q2432.2 (COL), Q2532.2 (COL), Q2632.2 (COL), Q2732.2 (COL), Q2832.2 (COL), Q2932.2 (COL), Q3032.2 (COL), Q3132.2 (COL), Q3232.2 (COL)
ROW01: JROW.1 (ROW01), Q0101.1 (ROW), Q0102.1 (ROW), Q0103.1 (ROW), Q0104.1 (ROW), Q0105.1 (ROW), Q0106.1 (ROW), Q0107.1 (ROW), Q0108.1 (ROW), Q0109.1 (ROW), Q0110.1 (ROW), Q0111.1 (ROW), Q0112.1 (ROW), Q0113.1 (ROW), Q0114.1 (ROW), Q0115.1 (ROW), Q0116.1 (ROW), Q0117.1 (ROW), Q0118.1 (ROW), Q0119.1 (ROW), Q0120.1 (ROW), Q0121.1 (ROW), Q0122.1 (ROW), Q0123.1 (ROW), Q0124.1 (ROW), Q0125.1 (ROW), Q0126.1 (ROW), Q0127.1 (ROW), Q0128.1 (ROW), Q0129.1 (ROW), Q0130.1 (ROW), Q0131.1 (ROW), Q0132.1 (ROW)
ROW02: JROW.2 (ROW02), Q0201.1 (ROW), Q0202.1 (ROW), Q0203.1 (ROW), Q0204.1 (ROW), Q0205.1 (ROW), Q0206.1 (ROW), Q0207.1 (ROW), Q0208.1 (ROW), Q0209.1 (ROW), Q0210.1 (ROW), Q0211.1 (ROW), Q0212.1 (ROW), Q0213.1 (ROW), Q0214.1 (ROW), Q0215.1 (ROW), Q0216.1 (ROW), Q0217.1 (ROW), Q0218.1 (ROW), Q0219.1 (ROW), Q0220.1 (ROW), Q0221.1 (ROW), Q0222.1 (ROW), Q0223.1 (ROW), Q0224.1 (ROW), Q0225.1 (ROW), Q0226.1 (ROW), Q0227.1 (ROW), Q0228.1 (ROW), Q0229.1 (ROW), Q0230.1 (ROW), Q0231.1 (ROW), Q0232.1 (ROW)
ROW03: JROW.3 (ROW03), Q0301.1 (ROW), Q0302.1 (ROW), Q0303.1 (ROW), Q0304.1 (ROW), Q0305.1 (ROW), Q0306.1 (ROW), Q0307.1 (ROW), Q0308.1 (ROW), Q0309.1 (ROW), Q0310.1 (ROW), Q0311.1 (ROW), Q0312.1 (ROW), Q0313.1 (ROW), Q0314.1 (ROW), Q0315.1 (ROW), Q0316.1 (ROW), Q0317.1 (ROW), Q0318.1 (ROW), Q0319.1 (ROW), Q0320.1 (ROW), Q0321.1 (ROW), Q0322.1 (ROW), Q0323.1 (ROW), Q0324.1 (ROW), Q0325.1 (ROW), Q0326.1 (ROW), Q0327.1 (ROW), Q0328.1 (ROW), Q0329.1 (ROW), Q0330.1 (ROW), Q0331.1 (ROW), Q0332.1 (ROW)
ROW04: JROW.4 (ROW04), Q0401.1 (ROW), Q0402.1 (ROW), Q0403.1 (ROW), Q0404.1 (ROW), Q0405.1 (ROW), Q0406.1 (ROW), Q0407.1 (ROW), Q0408.1 (ROW), Q0409.1 (ROW), Q0410.1 (ROW), Q0411.1 (ROW), Q0412.1 (ROW), Q0413.1 (ROW), Q0414.1 (ROW), Q0415.1 (ROW), Q0416.1 (ROW), Q0417.1 (ROW), Q0418.1 (ROW), Q0419.1 (ROW), Q0420.1 (ROW), Q0421.1 (ROW), Q0422.1 (ROW), Q0423.1 (ROW), Q0424.1 (ROW), Q0425.1 (ROW), Q0426.1 (ROW), Q0427.1 (ROW), Q0428.1 (ROW), Q0429.1 (ROW), Q0430.1 (ROW), Q0431.1 (ROW), Q0432.1 (ROW)
ROW05: JROW.5 (ROW05), Q0501.1 (ROW), Q0502.1 (ROW), Q0503.1 (ROW), Q0504.1 (ROW), Q0505.1 (ROW), Q0506.1 (ROW), Q0507.1 (ROW), Q0508.1 (ROW), Q0509.1 (ROW), Q0510.1 (ROW), Q0511.1 (ROW), Q0512.1 (ROW), Q0513.1 (ROW), Q0514.1 (ROW), Q0515.1 (ROW), Q0516.1 (ROW), Q0517.1 (ROW), Q0518.1 (ROW), Q0519.1 (ROW), Q0520.1 (ROW), Q0521.1 (ROW), Q0522.1 (ROW), Q0523.1 (ROW), Q0524.1 (ROW), Q0525.1 (ROW), Q0526.1 (ROW), Q0527.1 (ROW), Q0528.1 (ROW), Q0529.1 (ROW), Q0530.1 (ROW), Q0531.1 (ROW), Q0532.1 (ROW)
ROW06: JROW.6 (ROW06), Q0601.1 (ROW), Q0602.1 (ROW), Q0603.1 (ROW), Q0604.1 (ROW), Q0605.1 (ROW), Q0606.1 (ROW), Q0607.1 (ROW), Q0608.1 (ROW), Q0609.1 (ROW), Q0610.1 (ROW), Q0611.1 (ROW), Q0612.1 (ROW), Q0613.1 (ROW), Q0614.1 (ROW), Q0615.1 (ROW), Q0616.1 (ROW), Q0617.1 (ROW), Q0618.1 (ROW), Q0619.1 (ROW), Q0620.1 (ROW), Q0621.1 (ROW), Q0622.1 (ROW), Q0623.1 (ROW), Q0624.1 (ROW), Q0625.1 (ROW), Q0626.1 (ROW), Q0627.1 (ROW), Q0628.1 (ROW), Q0629.1 (ROW), Q0630.1 (ROW), Q0631.1 (ROW), Q0632.1 (ROW)
ROW07: JROW.7 (ROW07), Q0701.1 (ROW), Q0702.1 (ROW), Q0703.1 (ROW), Q0704.1 (ROW), Q0705.1 (ROW), Q0706.1 (ROW), Q0707.1 (ROW), Q0708.1 (ROW), Q0709.1 (ROW), Q0710.1 (ROW), Q0711.1 (ROW), Q0712.1 (ROW), Q0713.1 (ROW), Q0714.1 (ROW), Q0715.1 (ROW), Q0716.1 (ROW), Q0717.1 (ROW), Q0718.1 (ROW), Q0719.1 (ROW), Q0720.1 (ROW), Q0721.1 (ROW), Q0722.1 (ROW), Q0723.1 (ROW), Q0724.1 (ROW), Q0725.1 (ROW), Q0726.1 (ROW), Q0727.1 (ROW), Q0728.1 (ROW), Q0729.1 (ROW), Q0730.1 (ROW), Q0731.1 (ROW), Q0732.1 (ROW)
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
